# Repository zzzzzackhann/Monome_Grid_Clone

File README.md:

FOR NEXT TIME:

1. Find an LED driver than operates the same way your logic decoder works for easier wiring

2. Don't need shutdown pin control for LED driver

3. Better to have one interrupt enabled from the button demux. 

4. The rows aren't connected at all between the board and the MCU! Have to add 8 row pins for the button presses. 

5. Make the ATMega328PB a normal 328P, and also make sure it's not a QFN package!

6. See about using smaller JST connectors instead of ribbon cables. 

7. New, more stable USB-c recepticle

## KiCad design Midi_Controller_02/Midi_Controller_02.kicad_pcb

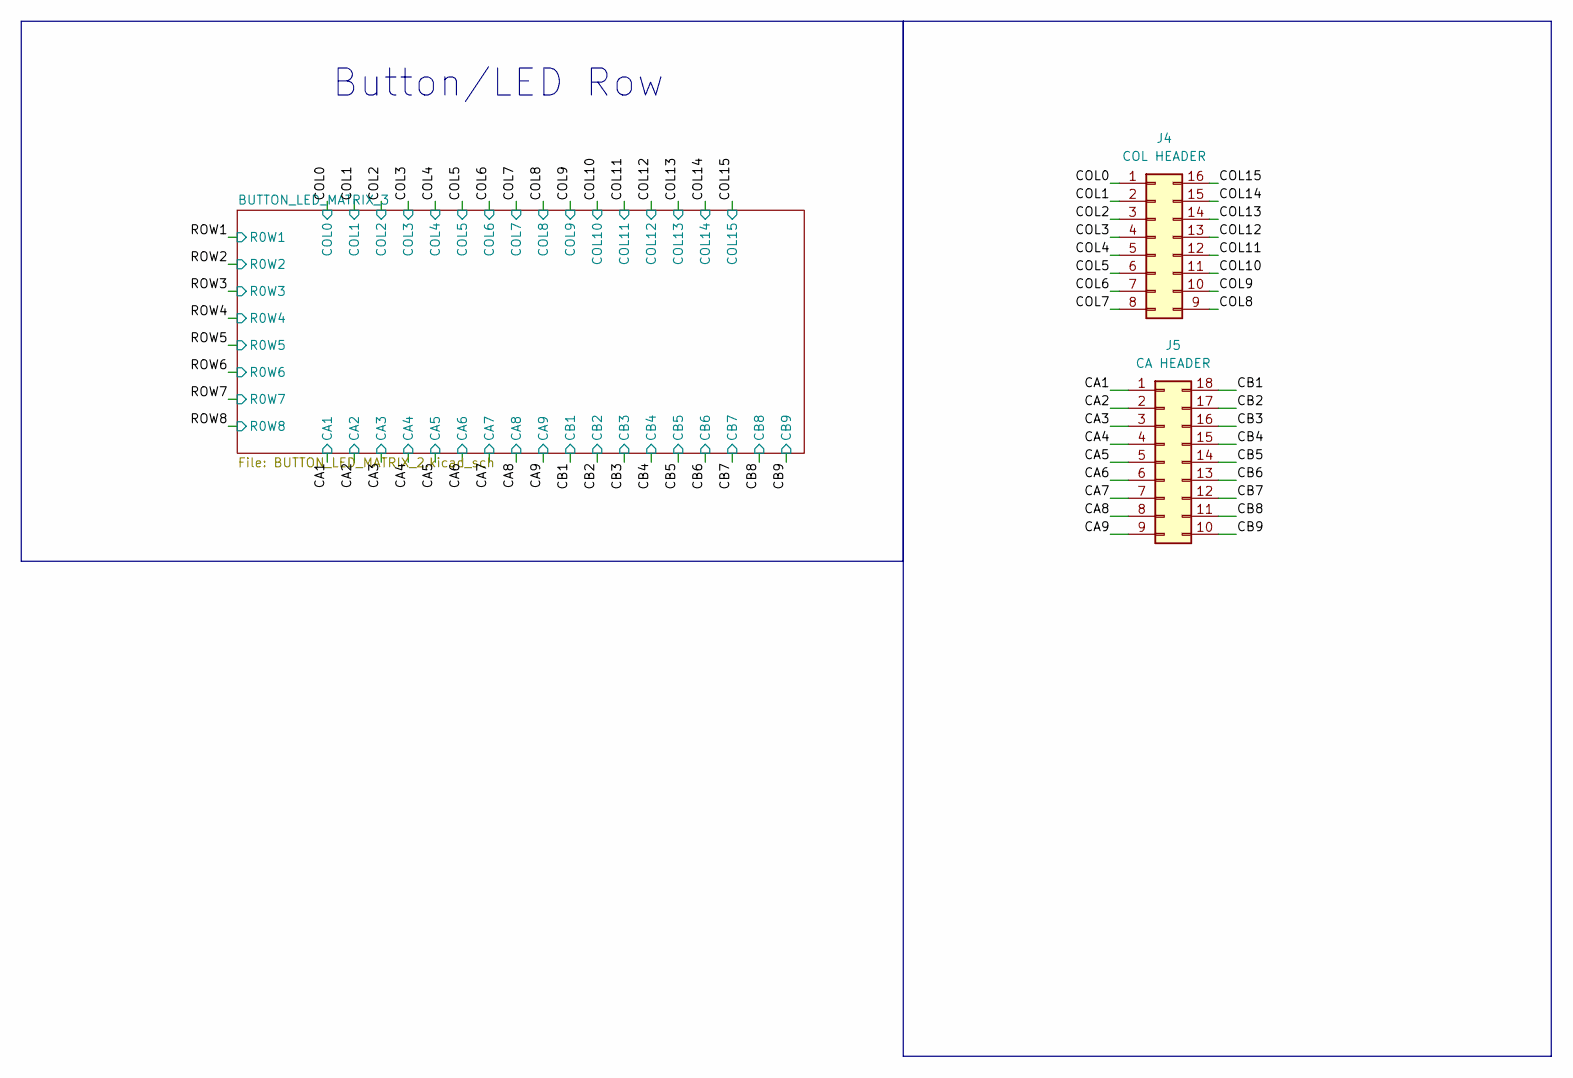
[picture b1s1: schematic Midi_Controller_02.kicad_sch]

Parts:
J4: COL HEADER; PinHeader_2x08_P2.54mm_Vertical
J5: CA HEADER; PinHeader_2x09_P2.54mm_Vertical

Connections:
/CONTROLLER-MATRIX/CA1: J5.1; also elsewhere on the board
/CONTROLLER-MATRIX/CA2: J5.2; also elsewhere on the board
/CONTROLLER-MATRIX/CA3: J5.3; also elsewhere on the board
/CONTROLLER-MATRIX/CA4: J5.4; also elsewhere on the board
/CONTROLLER-MATRIX/CA5: J5.5; also elsewhere on the board
/CONTROLLER-MATRIX/CA6: J5.6; also elsewhere on the board
/CONTROLLER-MATRIX/CA7: J5.7; also elsewhere on the board
/CONTROLLER-MATRIX/CA8: J5.8; also elsewhere on the board
/CONTROLLER-MATRIX/CA9: J5.9; also elsewhere on the board
/CONTROLLER-MATRIX/CB1: J5.18; also elsewhere on the board
/CONTROLLER-MATRIX/CB2: J5.17; also elsewhere on the board
/CONTROLLER-MATRIX/CB3: J5.16; also elsewhere on the board
/CONTROLLER-MATRIX/CB4: J5.15; also elsewhere on the board
/CONTROLLER-MATRIX/CB5: J5.14; also elsewhere on the board
/CONTROLLER-MATRIX/CB6: J5.13; also elsewhere on the board
/CONTROLLER-MATRIX/CB7: J5.12; also elsewhere on the board
/CONTROLLER-MATRIX/CB8: J5.11; also elsewhere on the board
/CONTROLLER-MATRIX/CB9: J5.10; also elsewhere on the board
/CONTROLLER-MATRIX/COL0: J4.1; also elsewhere on the board
/CONTROLLER-MATRIX/COL1: J4.2; also elsewhere on the board
/CONTROLLER-MATRIX/COL2: J4.3; also elsewhere on the board
/CONTROLLER-MATRIX/COL3: J4.4; also elsewhere on the board
/CONTROLLER-MATRIX/COL4: J4.5; also elsewhere on the board
/CONTROLLER-MATRIX/COL5: J4.6; also elsewhere on the board
/CONTROLLER-MATRIX/COL6: J4.7; also elsewhere on the board
/CONTROLLER-MATRIX/COL7: J4.8; also elsewhere on the board
/CONTROLLER-MATRIX/COL8: J4.9; also elsewhere on the board
/CONTROLLER-MATRIX/COL9: J4.10; also elsewhere on the board
/CONTROLLER-MATRIX/COL10: J4.11; also elsewhere on the board
/CONTROLLER-MATRIX/COL11: J4.12; also elsewhere on the board
/CONTROLLER-MATRIX/COL12: J4.13; also elsewhere on the board
/CONTROLLER-MATRIX/COL13: J4.14; also elsewhere on the board
/CONTROLLER-MATRIX/COL14: J4.15; also elsewhere on the board
/CONTROLLER-MATRIX/COL15: J4.16; also elsewhere on the board

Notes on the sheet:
Button/LED Row

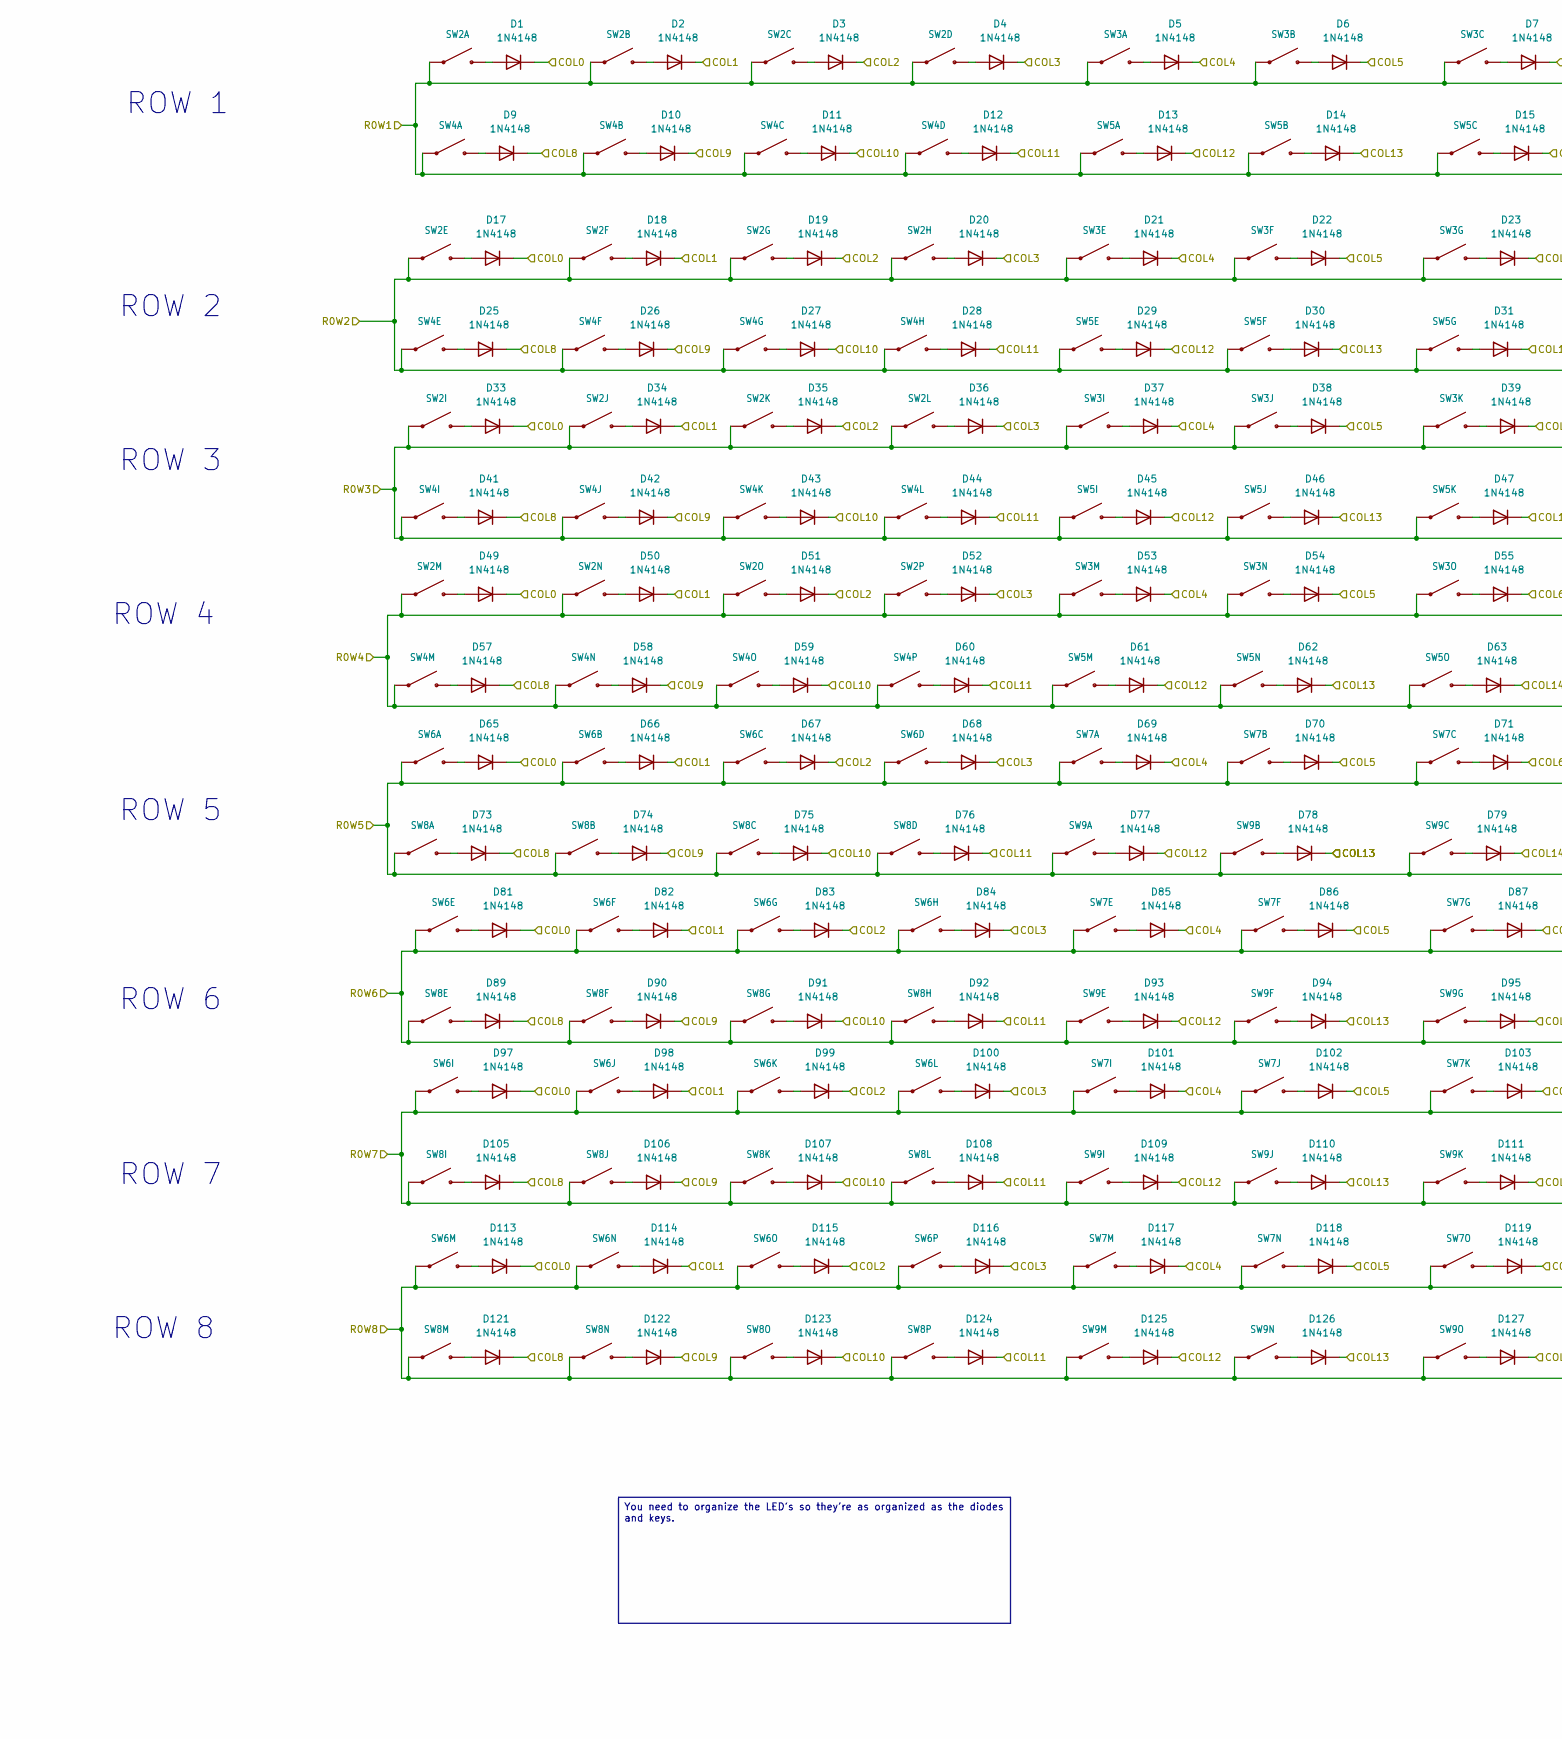
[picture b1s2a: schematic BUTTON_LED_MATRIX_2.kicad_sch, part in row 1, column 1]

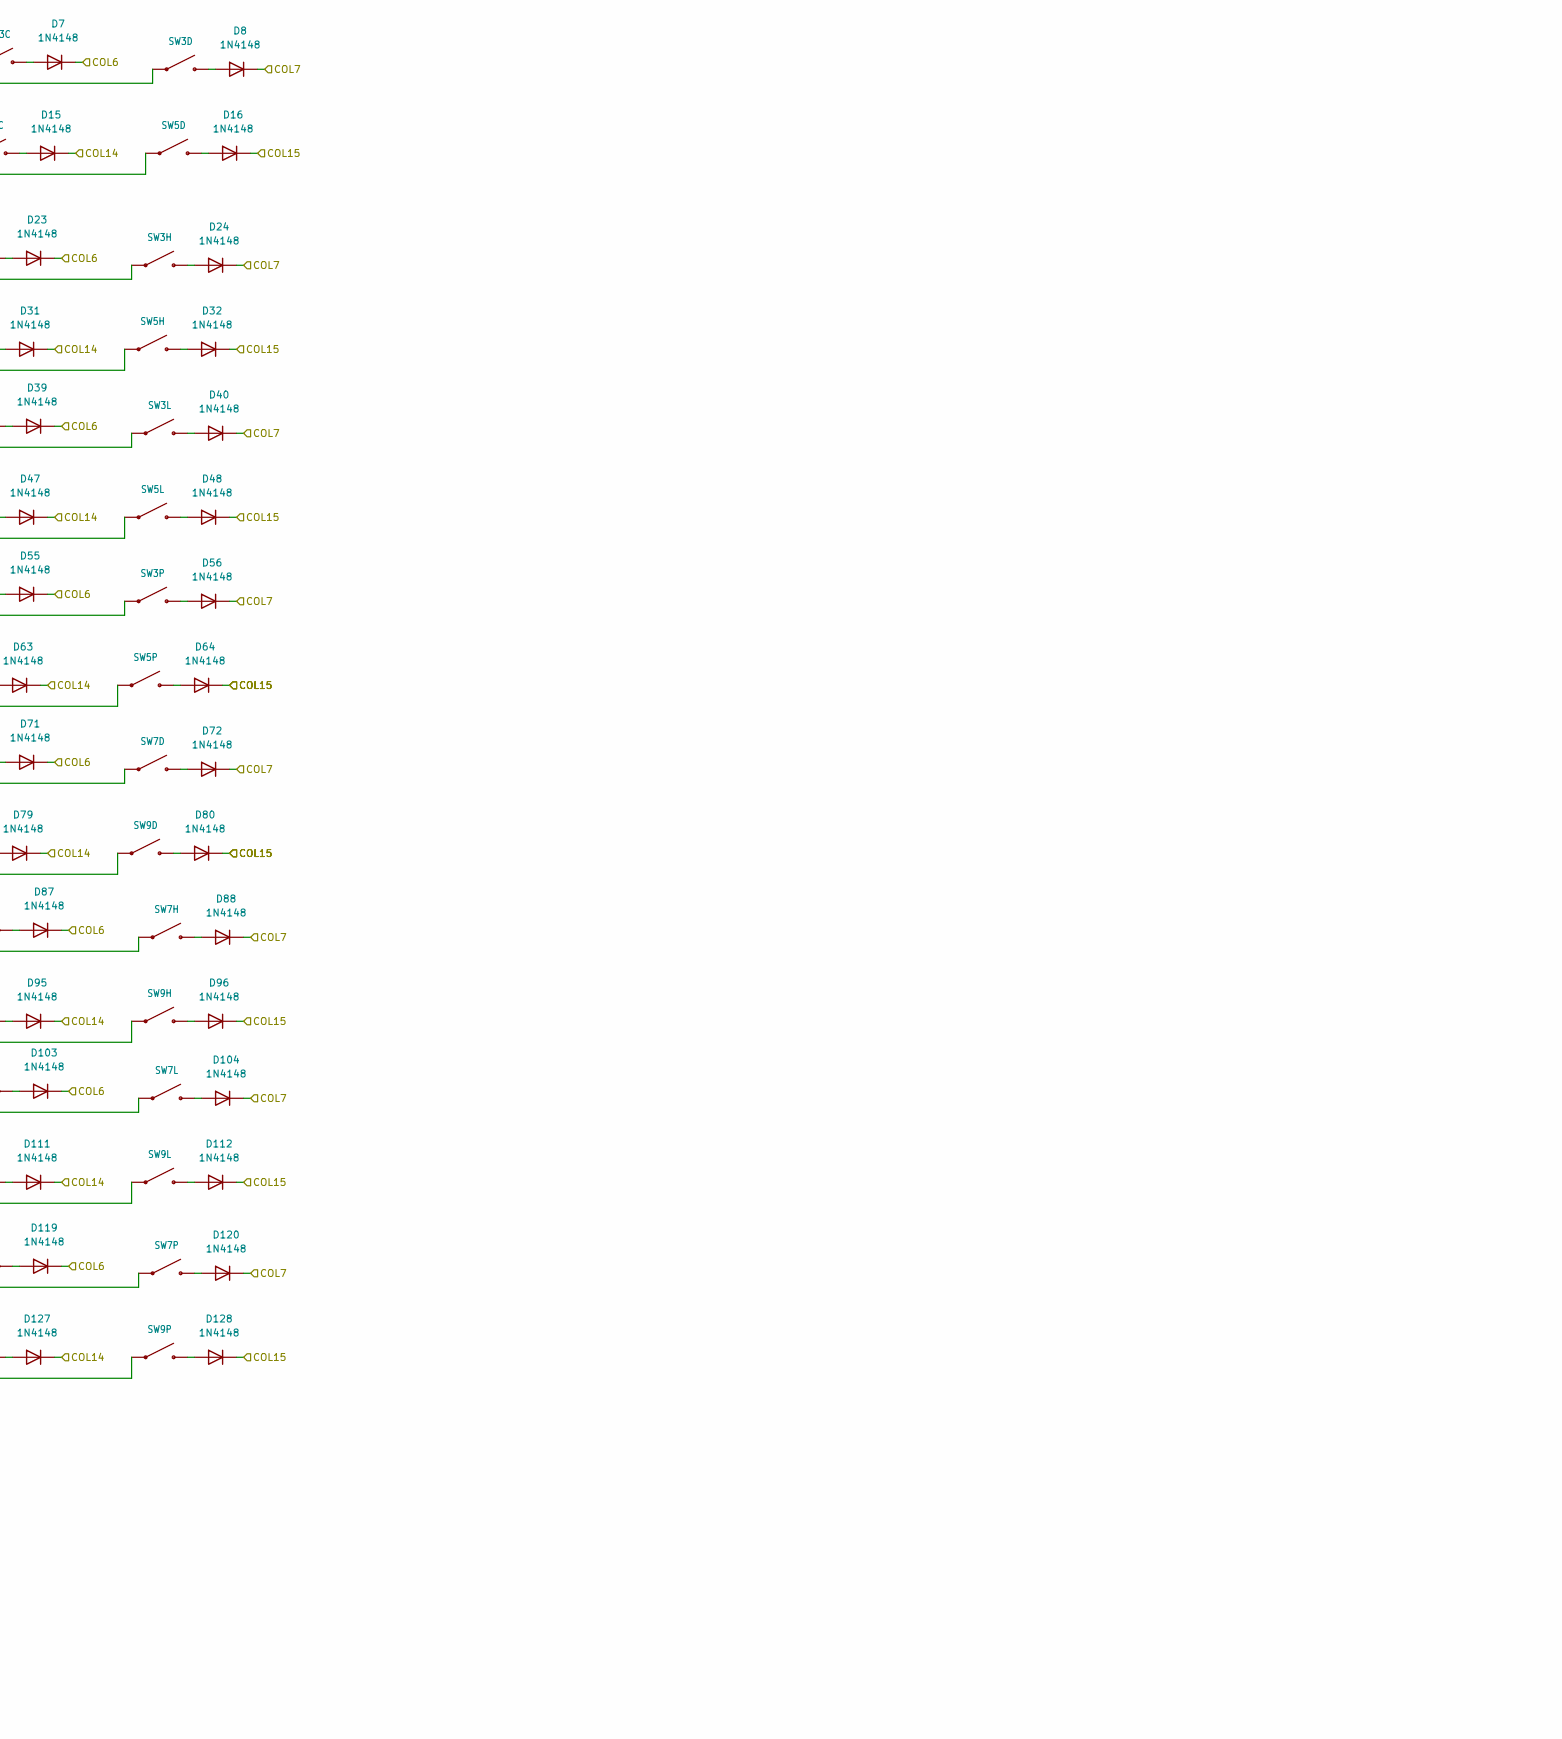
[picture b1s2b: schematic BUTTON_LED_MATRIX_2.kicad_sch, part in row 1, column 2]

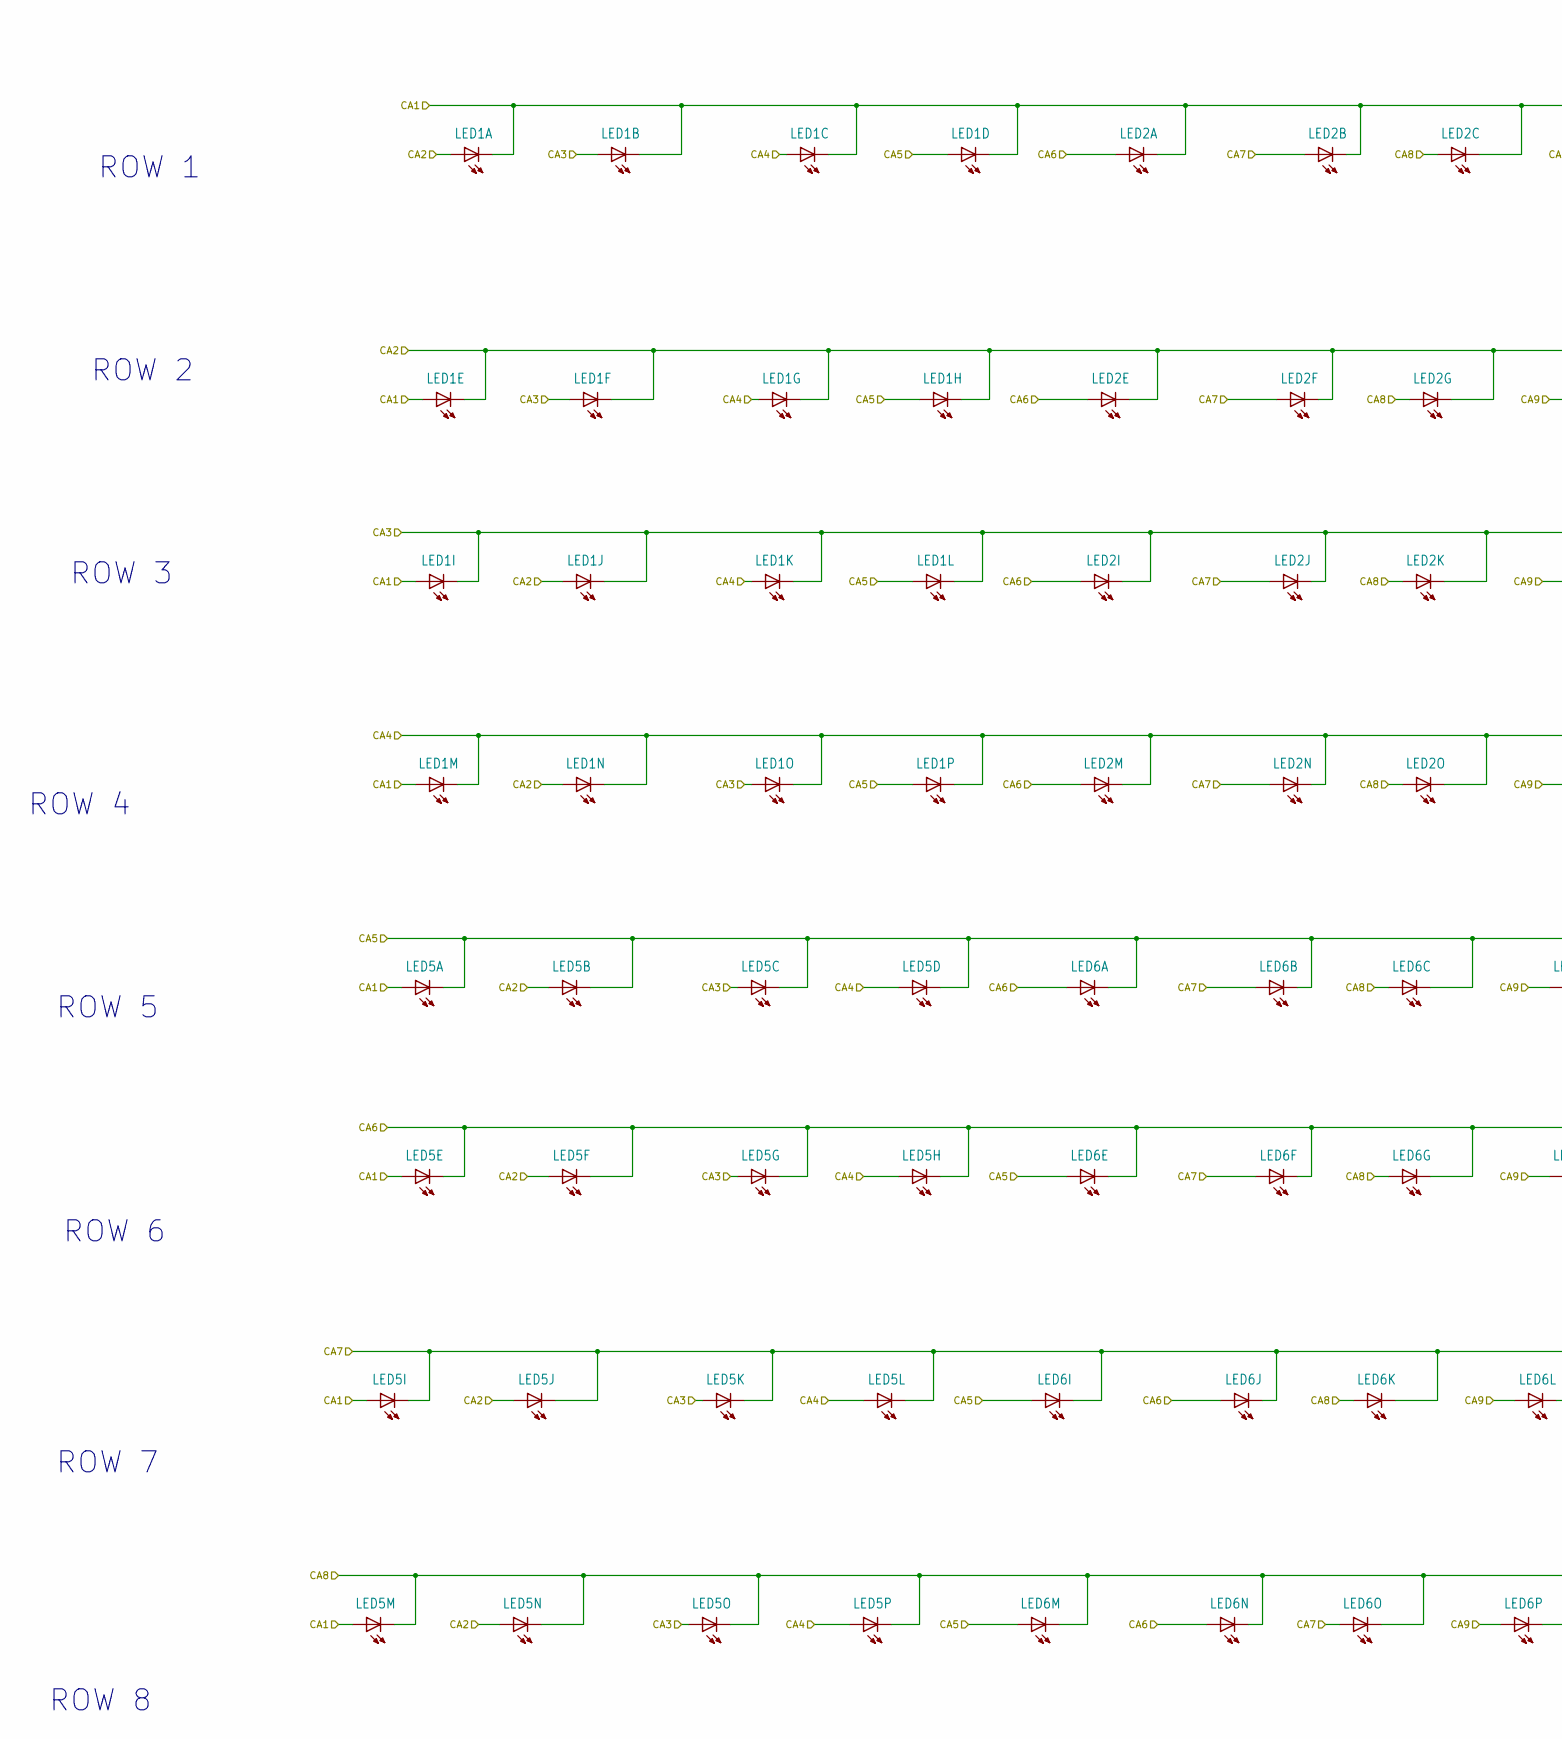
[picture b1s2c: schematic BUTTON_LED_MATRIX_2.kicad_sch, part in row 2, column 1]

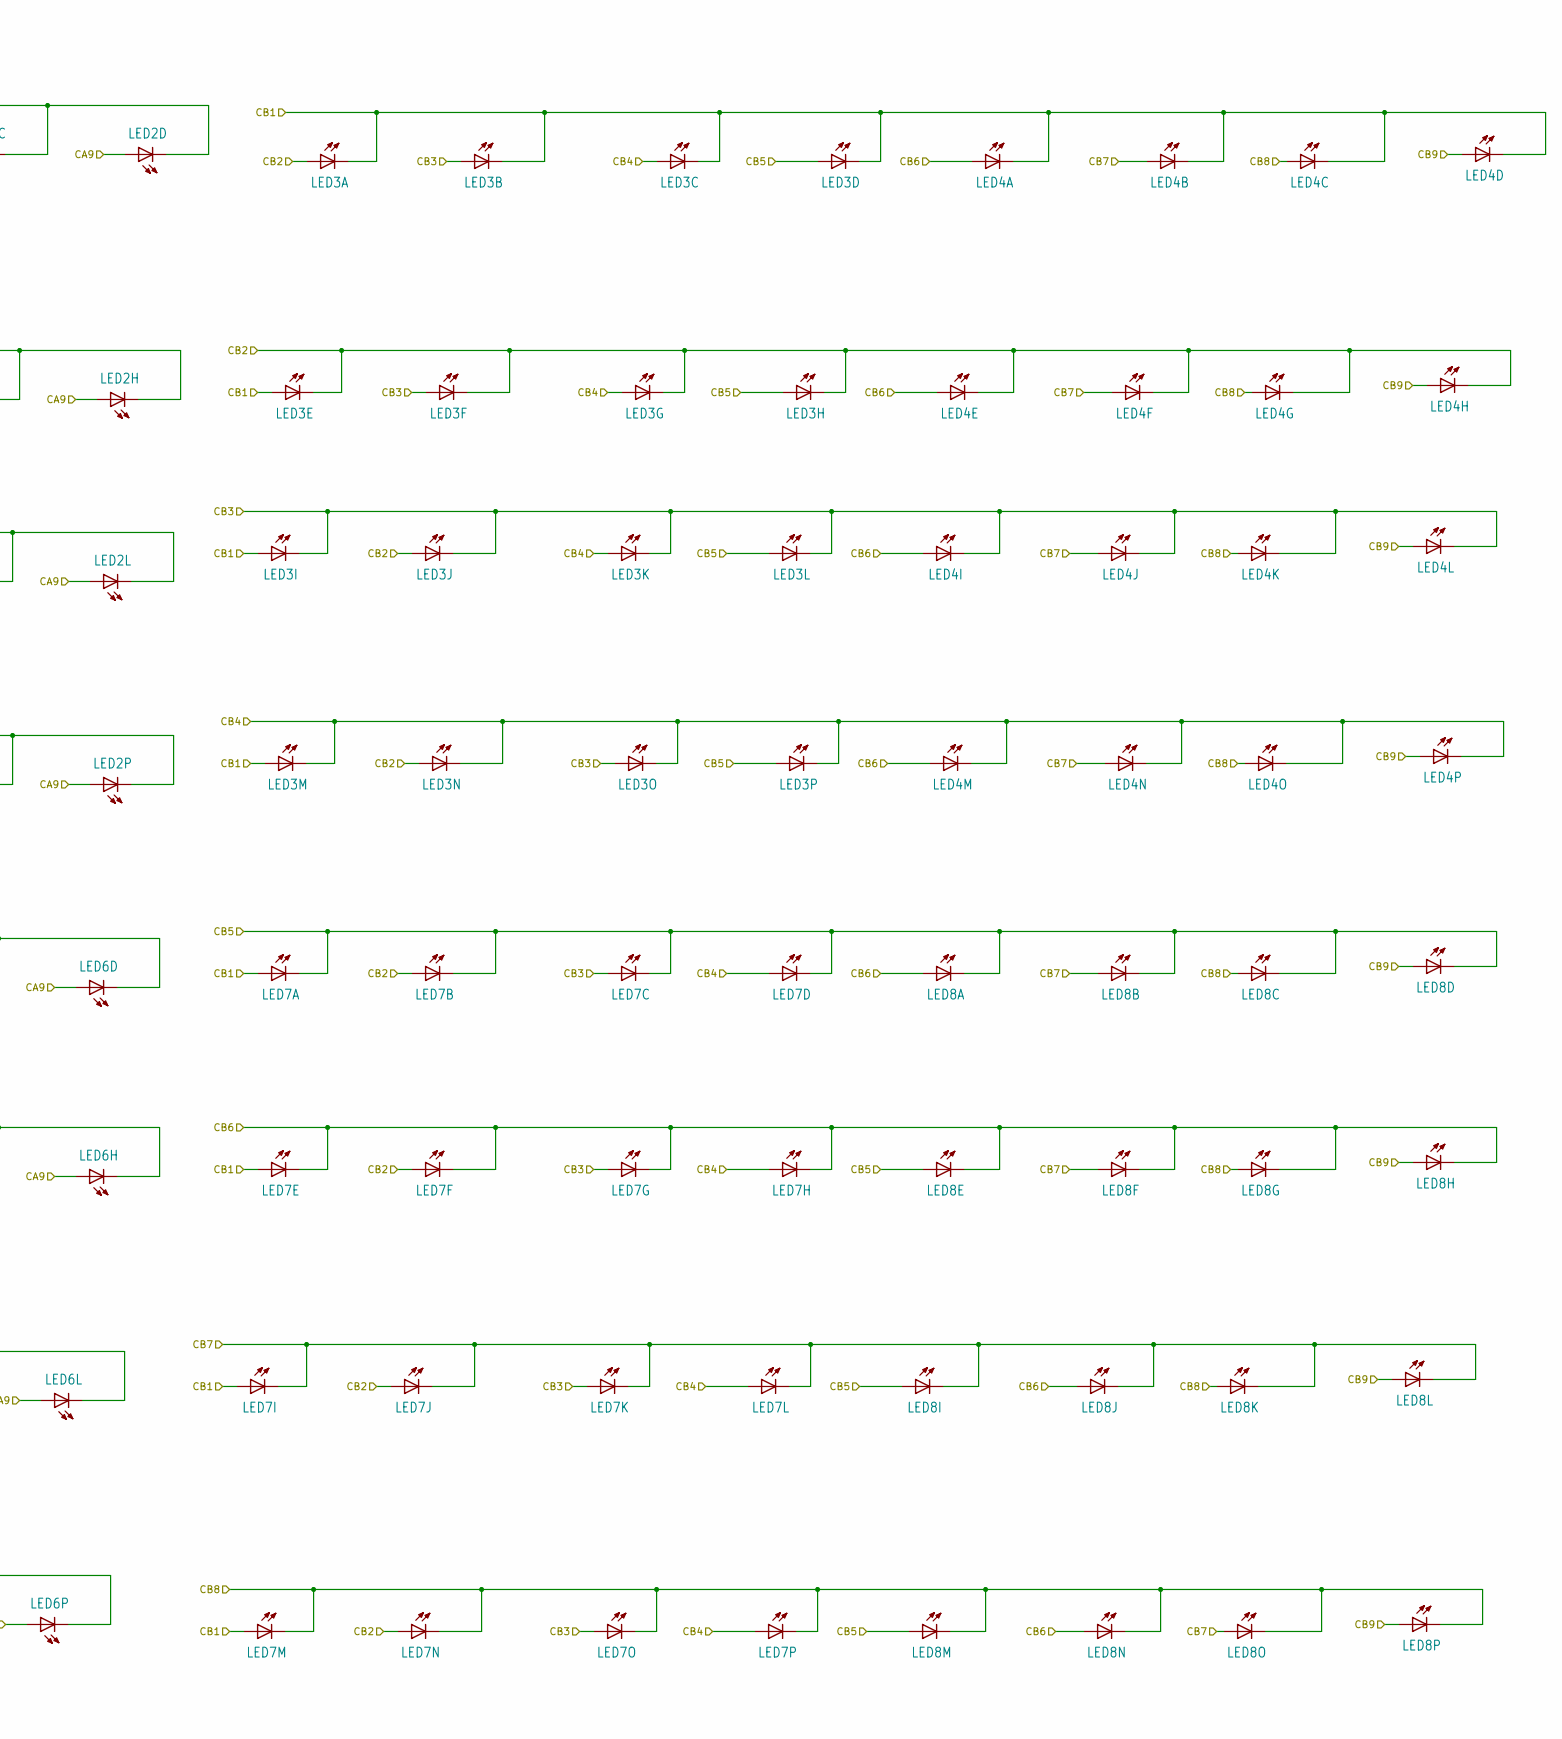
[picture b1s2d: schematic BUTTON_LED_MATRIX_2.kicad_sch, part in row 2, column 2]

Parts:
D1, D2, D3, D4, D5, D6, D7, D8, D9, D10, D11, D12, D13, D14, D15, D16, D17, D18, D19, D20, D21, D22, D23, D24, D25, D26, D27, D28, D29, D30, D31, D32, D33, D34, D35, D36, D37, D38, D39, D40, D41, D42, D43, D44, D45, D46, D47, D48, D49, D50, D51, D52, D53, D54, D55, D56, D57, D58, D59, D60, D61, D62, D63, D64, D65, D66, D67, D68, D69, D70, D71, D72, D73, D74, D75, D76, D77, D78, D79, D80, D81, D82, D83, D84, D85, D86, D87, D88, D89, D90, D91, D92, D93, D94, D95, D96, D97, D98, D99, D100, D101, D102, D103, D104, D105, D106, D107, D108, D109, D110, D111, D112, D113, D114, D115, D116, D117, D118, D119, D120, D121, D122, D123, D124, D125, D126, D127, D128: 1N4148; D_SOD-123
LED1, LED2, LED3, LED4, LED5, LED6, LED7, LED8: LED3MM-4X4GRID
SW2, SW3, SW4, SW5, SW6, SW7, SW8, SW9: ELAST_PAD_SQUARE_10MM_5.4MM_4X4GRID

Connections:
/CONTROLLER-MATRIX/CA1: LED1.A5 (A), LED1.A9 (A), LED1.A13 (A), LED1.K1 (C), LED1.K2 (C), LED1.K3 (C), LED1.K4 (C), LED2.K1 (C), LED2.K2 (C), LED2.K3 (C), LED2.K4 (C), LED5.A1 (A), LED5.A5 (A), LED5.A9 (A), LED5.A13 (A); also elsewhere on the board
/CONTROLLER-MATRIX/CA2: LED1.A1 (A), LED1.A10 (A), LED1.A14 (A), LED1.K5 (C), LED1.K6 (C), LED1.K7 (C), LED1.K8 (C), LED2.K5 (C), LED2.K6 (C), LED2.K7 (C), LED2.K8 (C), LED5.A2 (A), LED5.A6 (A), LED5.A10 (A), LED5.A14 (A); also elsewhere on the board
/CONTROLLER-MATRIX/CA3: LED1.A2 (A), LED1.A6 (A), LED1.A15 (A), LED1.K9 (C), LED1.K10 (C), LED1.K11 (C), LED1.K12 (C), LED2.K9 (C), LED2.K10 (C), LED2.K11 (C), LED2.K12 (C), LED5.A3 (A), LED5.A7 (A), LED5.A11 (A), LED5.A15 (A); also elsewhere on the board
/CONTROLLER-MATRIX/CA4: LED1.A3 (A), LED1.A7 (A), LED1.A11 (A), LED1.K13 (C), LED1.K14 (C), LED1.K15 (C), LED1.K16 (C), LED2.K13 (C), LED2.K14 (C), LED2.K15 (C), LED2.K16 (C), LED5.A4 (A), LED5.A8 (A), LED5.A12 (A), LED5.A16 (A); also elsewhere on the board
/CONTROLLER-MATRIX/CA5: LED1.A4 (A), LED1.A8 (A), LED1.A12 (A), LED1.A16 (A), LED5.K1 (C), LED5.K2 (C), LED5.K3 (C), LED5.K4 (C), LED6.A5 (A), LED6.A9 (A), LED6.A13 (A), LED6.K1 (C), LED6.K2 (C), LED6.K3 (C), LED6.K4 (C); also elsewhere on the board
/CONTROLLER-MATRIX/CA6: LED2.A1 (A), LED2.A5 (A), LED2.A9 (A), LED2.A13 (A), LED5.K5 (C), LED5.K6 (C), LED5.K7 (C), LED5.K8 (C), LED6.A1 (A), LED6.A10 (A), LED6.A14 (A), LED6.K5 (C), LED6.K6 (C), LED6.K7 (C), LED6.K8 (C); also elsewhere on the board
/CONTROLLER-MATRIX/CA7: LED2.A2 (A), LED2.A6 (A), LED2.A10 (A), LED2.A14 (A), LED5.K9 (C), LED5.K10 (C), LED5.K11 (C), LED5.K12 (C), LED6.A2 (A), LED6.A6 (A), LED6.A15 (A), LED6.K9 (C), LED6.K10 (C), LED6.K11 (C), LED6.K12 (C); also elsewhere on the board
/CONTROLLER-MATRIX/CA8: LED2.A3 (A), LED2.A7 (A), LED2.A11 (A), LED2.A15 (A), LED5.K13 (C), LED5.K14 (C), LED5.K15 (C), LED5.K16 (C), LED6.A3 (A), LED6.A7 (A), LED6.A11 (A), LED6.K13 (C), LED6.K14 (C), LED6.K15 (C), LED6.K16 (C); also elsewhere on the board
/CONTROLLER-MATRIX/CA9: LED2.A4 (A), LED2.A8 (A), LED2.A12 (A), LED2.A16 (A), LED6.A4 (A), LED6.A8 (A), LED6.A12 (A), LED6.A16 (A); also elsewhere on the board
/CONTROLLER-MATRIX/CB1: LED3.A5 (A), LED3.A9 (A), LED3.A13 (A), LED3.K1 (C), LED3.K2 (C), LED3.K3 (C), LED3.K4 (C), LED4.K1 (C), LED4.K2 (C), LED4.K3 (C), LED4.K4 (C), LED7.A1 (A), LED7.A5 (A), LED7.A9 (A), LED7.A13 (A); also elsewhere on the board
/CONTROLLER-MATRIX/CB2: LED3.A1 (A), LED3.A10 (A), LED3.A14 (A), LED3.K5 (C), LED3.K6 (C), LED3.K7 (C), LED3.K8 (C), LED4.K5 (C), LED4.K6 (C), LED4.K7 (C), LED4.K8 (C), LED7.A2 (A), LED7.A6 (A), LED7.A10 (A), LED7.A14 (A); also elsewhere on the board
/CONTROLLER-MATRIX/CB3: LED3.A2 (A), LED3.A6 (A), LED3.A15 (A), LED3.K9 (C), LED3.K10 (C), LED3.K11 (C), LED3.K12 (C), LED4.K9 (C), LED4.K10 (C), LED4.K11 (C), LED4.K12 (C), LED7.A3 (A), LED7.A7 (A), LED7.A11 (A), LED7.A15 (A); also elsewhere on the board
/CONTROLLER-MATRIX/CB4: LED3.A3 (A), LED3.A7 (A), LED3.A11 (A), LED3.K13 (C), LED3.K14 (C), LED3.K15 (C), LED3.K16 (C), LED4.K13 (C), LED4.K14 (C), LED4.K15 (C), LED4.K16 (C), LED7.A4 (A), LED7.A8 (A), LED7.A12 (A), LED7.A16 (A); also elsewhere on the board
/CONTROLLER-MATRIX/CB5: LED3.A4 (A), LED3.A8 (A), LED3.A12 (A), LED3.A16 (A), LED7.K1 (C), LED7.K2 (C), LED7.K3 (C), LED7.K4 (C), LED8.A5 (A), LED8.A9 (A), LED8.A13 (A), LED8.K1 (C), LED8.K2 (C), LED8.K3 (C), LED8.K4 (C); also elsewhere on the board
/CONTROLLER-MATRIX/CB6: LED4.A1 (A), LED4.A5 (A), LED4.A9 (A), LED4.A13 (A), LED7.K5 (C), LED7.K6 (C), LED7.K7 (C), LED7.K8 (C), LED8.A1 (A), LED8.A10 (A), LED8.A14 (A), LED8.K5 (C), LED8.K6 (C), LED8.K7 (C), LED8.K8 (C); also elsewhere on the board
/CONTROLLER-MATRIX/CB7: LED4.A2 (A), LED4.A6 (A), LED4.A10 (A), LED4.A14 (A), LED7.K9 (C), LED7.K10 (C), LED7.K11 (C), LED7.K12 (C), LED8.A2 (A), LED8.A6 (A), LED8.A15 (A), LED8.K9 (C), LED8.K10 (C), LED8.K11 (C), LED8.K12 (C); also elsewhere on the board
/CONTROLLER-MATRIX/CB8: LED4.A3 (A), LED4.A7 (A), LED4.A11 (A), LED4.A15 (A), LED7.K13 (C), LED7.K14 (C), LED7.K15 (C), LED7.K16 (C), LED8.A3 (A), LED8.A7 (A), LED8.A11 (A), LED8.K13 (C), LED8.K14 (C), LED8.K15 (C), LED8.K16 (C); also elsewhere on the board
/CONTROLLER-MATRIX/CB9: LED4.A4 (A), LED4.A8 (A), LED4.A12 (A), LED4.A16 (A), LED8.A4 (A), LED8.A8 (A), LED8.A12 (A), LED8.A16 (A); also elsewhere on the board
/CONTROLLER-MATRIX/COL0: D1.1 (K), D17.1 (K), D33.1 (K), D49.1 (K), D65.1 (K), D81.1 (K), D97.1 (K), D113.1 (K); also elsewhere on the board
/CONTROLLER-MATRIX/COL1: D2.1 (K), D18.1 (K), D34.1 (K), D50.1 (K), D66.1 (K), D82.1 (K), D98.1 (K), D114.1 (K); also elsewhere on the board
/CONTROLLER-MATRIX/COL2: D3.1 (K), D19.1 (K), D35.1 (K), D51.1 (K), D67.1 (K), D83.1 (K), D99.1 (K), D115.1 (K); also elsewhere on the board
/CONTROLLER-MATRIX/COL3: D4.1 (K), D20.1 (K), D36.1 (K), D52.1 (K), D68.1 (K), D84.1 (K), D100.1 (K), D116.1 (K); also elsewhere on the board
/CONTROLLER-MATRIX/COL4: D5.1 (K), D21.1 (K), D37.1 (K), D53.1 (K), D69.1 (K), D85.1 (K), D101.1 (K), D117.1 (K); also elsewhere on the board
/CONTROLLER-MATRIX/COL5: D6.1 (K), D22.1 (K), D38.1 (K), D54.1 (K), D70.1 (K), D86.1 (K), D102.1 (K), D118.1 (K); also elsewhere on the board
/CONTROLLER-MATRIX/COL6: D7.1 (K), D23.1 (K), D39.1 (K), D55.1 (K), D71.1 (K), D87.1 (K), D103.1 (K), D119.1 (K); also elsewhere on the board
/CONTROLLER-MATRIX/COL7: D8.1 (K), D24.1 (K), D40.1 (K), D56.1 (K), D72.1 (K), D88.1 (K), D104.1 (K), D120.1 (K); also elsewhere on the board
/CONTROLLER-MATRIX/COL8: D9.1 (K), D25.1 (K), D41.1 (K), D57.1 (K), D73.1 (K), D89.1 (K), D105.1 (K), D121.1 (K); also elsewhere on the board
/CONTROLLER-MATRIX/COL9: D10.1 (K), D26.1 (K), D42.1 (K), D58.1 (K), D74.1 (K), D90.1 (K), D106.1 (K), D122.1 (K); also elsewhere on the board
/CONTROLLER-MATRIX/COL10: D11.1 (K), D27.1 (K), D43.1 (K), D59.1 (K), D75.1 (K), D91.1 (K), D107.1 (K), D123.1 (K); also elsewhere on the board
/CONTROLLER-MATRIX/COL11: D12.1 (K), D28.1 (K), D44.1 (K), D60.1 (K), D76.1 (K), D92.1 (K), D108.1 (K), D124.1 (K); also elsewhere on the board
/CONTROLLER-MATRIX/COL12: D13.1 (K), D29.1 (K), D45.1 (K), D61.1 (K), D77.1 (K), D93.1 (K), D109.1 (K), D125.1 (K); also elsewhere on the board
/CONTROLLER-MATRIX/COL13: D14.1 (K), D30.1 (K), D46.1 (K), D62.1 (K), D78.1 (K), D94.1 (K), D110.1 (K), D126.1 (K); also elsewhere on the board
/CONTROLLER-MATRIX/COL14: D15.1 (K), D31.1 (K), D47.1 (K), D63.1 (K), D79.1 (K), D95.1 (K), D111.1 (K), D127.1 (K); also elsewhere on the board
/CONTROLLER-MATRIX/COL15: D16.1 (K), D32.1 (K), D48.1 (K), D64.1 (K), D80.1 (K), D96.1 (K), D112.1 (K), D128.1 (K); also elsewhere on the board
/CONTROLLER-MATRIX/ROW1: SW2.A1, SW2.A2, SW2.A3, SW2.A4, SW3.A1, SW3.A2, SW3.A3, SW3.A4, SW4.A1, SW4.A2, SW4.A3, SW4.A4, SW5.A1, SW5.A2, SW5.A3, SW5.A4
/CONTROLLER-MATRIX/ROW2: SW2.A5, SW2.A6, SW2.A7, SW2.A8, SW3.A5, SW3.A6, SW3.A7, SW3.A8, SW4.A5, SW4.A6, SW4.A7, SW4.A8, SW5.A5, SW5.A6, SW5.A7, SW5.A8
/CONTROLLER-MATRIX/ROW3: SW2.A9, SW2.A10, SW2.A11, SW2.A12, SW3.A9, SW3.A10, SW3.A11, SW3.A12, SW4.A9, SW4.A10, SW4.A11, SW4.A12, SW5.A9, SW5.A10, SW5.A11, SW5.A12
/CONTROLLER-MATRIX/ROW4: SW2.A13, SW2.A14, SW2.A15, SW2.A16, SW3.A13, SW3.A14, SW3.A15, SW3.A16, SW4.A13, SW4.A14, SW4.A15, SW4.A16, SW5.A13, SW5.A14, SW5.A15, SW5.A16
/CONTROLLER-MATRIX/ROW5: SW6.A1, SW6.A2, SW6.A3, SW6.A4, SW7.A1, SW7.A2, SW7.A3, SW7.A4, SW8.A1, SW8.A2, SW8.A3, SW8.A4, SW9.A1, SW9.A2, SW9.A3, SW9.A4
/CONTROLLER-MATRIX/ROW6: SW6.A5, SW6.A6, SW6.A7, SW6.A8, SW7.A5, SW7.A6, SW7.A7, SW7.A8, SW8.A5, SW8.A6, SW8.A7, SW8.A8, SW9.A5, SW9.A6, SW9.A7, SW9.A8
/CONTROLLER-MATRIX/ROW7: SW6.A9, SW6.A10, SW6.A11, SW6.A12, SW7.A9, SW7.A10, SW7.A11, SW7.A12, SW8.A9, SW8.A10, SW8.A11, SW8.A12, SW9.A9, SW9.A10, SW9.A11, SW9.A12
/CONTROLLER-MATRIX/ROW8: SW6.A13, SW6.A14, SW6.A15, SW6.A16, SW7.A13, SW7.A14, SW7.A15, SW7.A16, SW8.A13, SW8.A14, SW8.A15, SW8.A16, SW9.A13, SW9.A14, SW9.A15, SW9.A16
unnamed: D1.2 (A), SW2.B1
unnamed: D2.2 (A), SW2.B2
unnamed: D3.2 (A), SW2.B3
unnamed: D4.2 (A), SW2.B4
unnamed: D5.2 (A), SW3.B1
unnamed: D6.2 (A), SW3.B2
unnamed: D7.2 (A), SW3.B3
unnamed: D8.2 (A), SW3.B4
unnamed: D9.2 (A), SW4.B1
unnamed: D10.2 (A), SW4.B2
unnamed: D11.2 (A), SW4.B3
unnamed: D12.2 (A), SW4.B4
unnamed: D13.2 (A), SW5.B1
unnamed: D14.2 (A), SW5.B2
unnamed: D15.2 (A), SW5.B3
unnamed: D16.2 (A), SW5.B4
unnamed: D17.2 (A), SW2.B5
unnamed: D18.2 (A), SW2.B6
unnamed: D19.2 (A), SW2.B7
unnamed: D20.2 (A), SW2.B8
unnamed: D21.2 (A), SW3.B5
unnamed: D22.2 (A), SW3.B6
unnamed: D23.2 (A), SW3.B7
unnamed: D24.2 (A), SW3.B8
unnamed: D25.2 (A), SW4.B5
unnamed: D26.2 (A), SW4.B6
unnamed: D27.2 (A), SW4.B7
unnamed: D28.2 (A), SW4.B8
unnamed: D29.2 (A), SW5.B5
unnamed: D30.2 (A), SW5.B6
unnamed: D31.2 (A), SW5.B7
unnamed: D32.2 (A), SW5.B8
unnamed: D33.2 (A), SW2.B9
unnamed: D34.2 (A), SW2.B10
unnamed: D35.2 (A), SW2.B11
unnamed: D36.2 (A), SW2.B12
unnamed: D37.2 (A), SW3.B9
unnamed: D38.2 (A), SW3.B10
unnamed: D39.2 (A), SW3.B11
unnamed: D40.2 (A), SW3.B12
unnamed: D41.2 (A), SW4.B9
unnamed: D42.2 (A), SW4.B10
unnamed: D43.2 (A), SW4.B11
unnamed: D44.2 (A), SW4.B12
unnamed: D45.2 (A), SW5.B9
unnamed: D46.2 (A), SW5.B10
unnamed: D47.2 (A), SW5.B11
unnamed: D48.2 (A), SW5.B12
unnamed: D49.2 (A), SW2.B13
unnamed: D50.2 (A), SW2.B14
unnamed: D51.2 (A), SW2.B15
unnamed: D52.2 (A), SW2.B16
unnamed: D53.2 (A), SW3.B13
unnamed: D54.2 (A), SW3.B14
unnamed: D55.2 (A), SW3.B15
unnamed: D56.2 (A), SW3.B16
unnamed: D57.2 (A), SW4.B13
unnamed: D58.2 (A), SW4.B14
unnamed: D59.2 (A), SW4.B15
unnamed: D60.2 (A), SW4.B16
unnamed: D61.2 (A), SW5.B13
unnamed: D62.2 (A), SW5.B14
unnamed: D63.2 (A), SW5.B15
unnamed: D64.2 (A), SW5.B16
unnamed: D65.2 (A), SW6.B1
unnamed: D66.2 (A), SW6.B2
unnamed: D67.2 (A), SW6.B3
unnamed: D68.2 (A), SW6.B4
unnamed: D69.2 (A), SW7.B1
unnamed: D70.2 (A), SW7.B2
unnamed: D71.2 (A), SW7.B3
unnamed: D72.2 (A), SW7.B4
unnamed: D73.2 (A), SW8.B1
unnamed: D74.2 (A), SW8.B2
unnamed: D75.2 (A), SW8.B3
unnamed: D76.2 (A), SW8.B4
unnamed: D77.2 (A), SW9.B1
unnamed: D78.2 (A), SW9.B2
unnamed: D79.2 (A), SW9.B3
unnamed: D80.2 (A), SW9.B4
unnamed: D81.2 (A), SW6.B5
unnamed: D82.2 (A), SW6.B6
unnamed: D83.2 (A), SW6.B7
unnamed: D84.2 (A), SW6.B8
unnamed: D85.2 (A), SW7.B5
unnamed: D86.2 (A), SW7.B6
unnamed: D87.2 (A), SW7.B7
unnamed: D88.2 (A), SW7.B8
unnamed: D89.2 (A), SW8.B5
unnamed: D90.2 (A), SW8.B6
unnamed: D91.2 (A), SW8.B7
unnamed: D92.2 (A), SW8.B8
unnamed: D93.2 (A), SW9.B5
unnamed: D94.2 (A), SW9.B6
unnamed: D95.2 (A), SW9.B7
unnamed: D96.2 (A), SW9.B8
unnamed: D97.2 (A), SW6.B9
unnamed: D98.2 (A), SW6.B10
unnamed: D99.2 (A), SW6.B11
unnamed: D100.2 (A), SW6.B12
unnamed: D101.2 (A), SW7.B9
unnamed: D102.2 (A), SW7.B10
unnamed: D103.2 (A), SW7.B11
unnamed: D104.2 (A), SW7.B12
unnamed: D105.2 (A), SW8.B9
unnamed: D106.2 (A), SW8.B10
unnamed: D107.2 (A), SW8.B11
unnamed: D108.2 (A), SW8.B12
unnamed: D109.2 (A), SW9.B9
unnamed: D110.2 (A), SW9.B10
unnamed: D111.2 (A), SW9.B11
unnamed: D112.2 (A), SW9.B12
unnamed: D113.2 (A), SW6.B13
unnamed: D114.2 (A), SW6.B14
unnamed: D115.2 (A), SW6.B15
unnamed: D116.2 (A), SW6.B16
unnamed: D117.2 (A), SW7.B13
unnamed: D118.2 (A), SW7.B14
unnamed: D119.2 (A), SW7.B15
unnamed: D120.2 (A), SW7.B16
unnamed: D121.2 (A), SW8.B13
unnamed: D122.2 (A), SW8.B14
unnamed: D123.2 (A), SW8.B15
unnamed: D124.2 (A), SW8.B16
unnamed: D125.2 (A), SW9.B13
unnamed: D126.2 (A), SW9.B14
unnamed: D127.2 (A), SW9.B15
unnamed: D128.2 (A), SW9.B16

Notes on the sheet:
ROW 7
ROW 6
ROW 3
ROW 2
ROW 8
ROW 4
ROW 5
ROW 1
You need to organize the LED's so they're as organized as the diodes and keys.
